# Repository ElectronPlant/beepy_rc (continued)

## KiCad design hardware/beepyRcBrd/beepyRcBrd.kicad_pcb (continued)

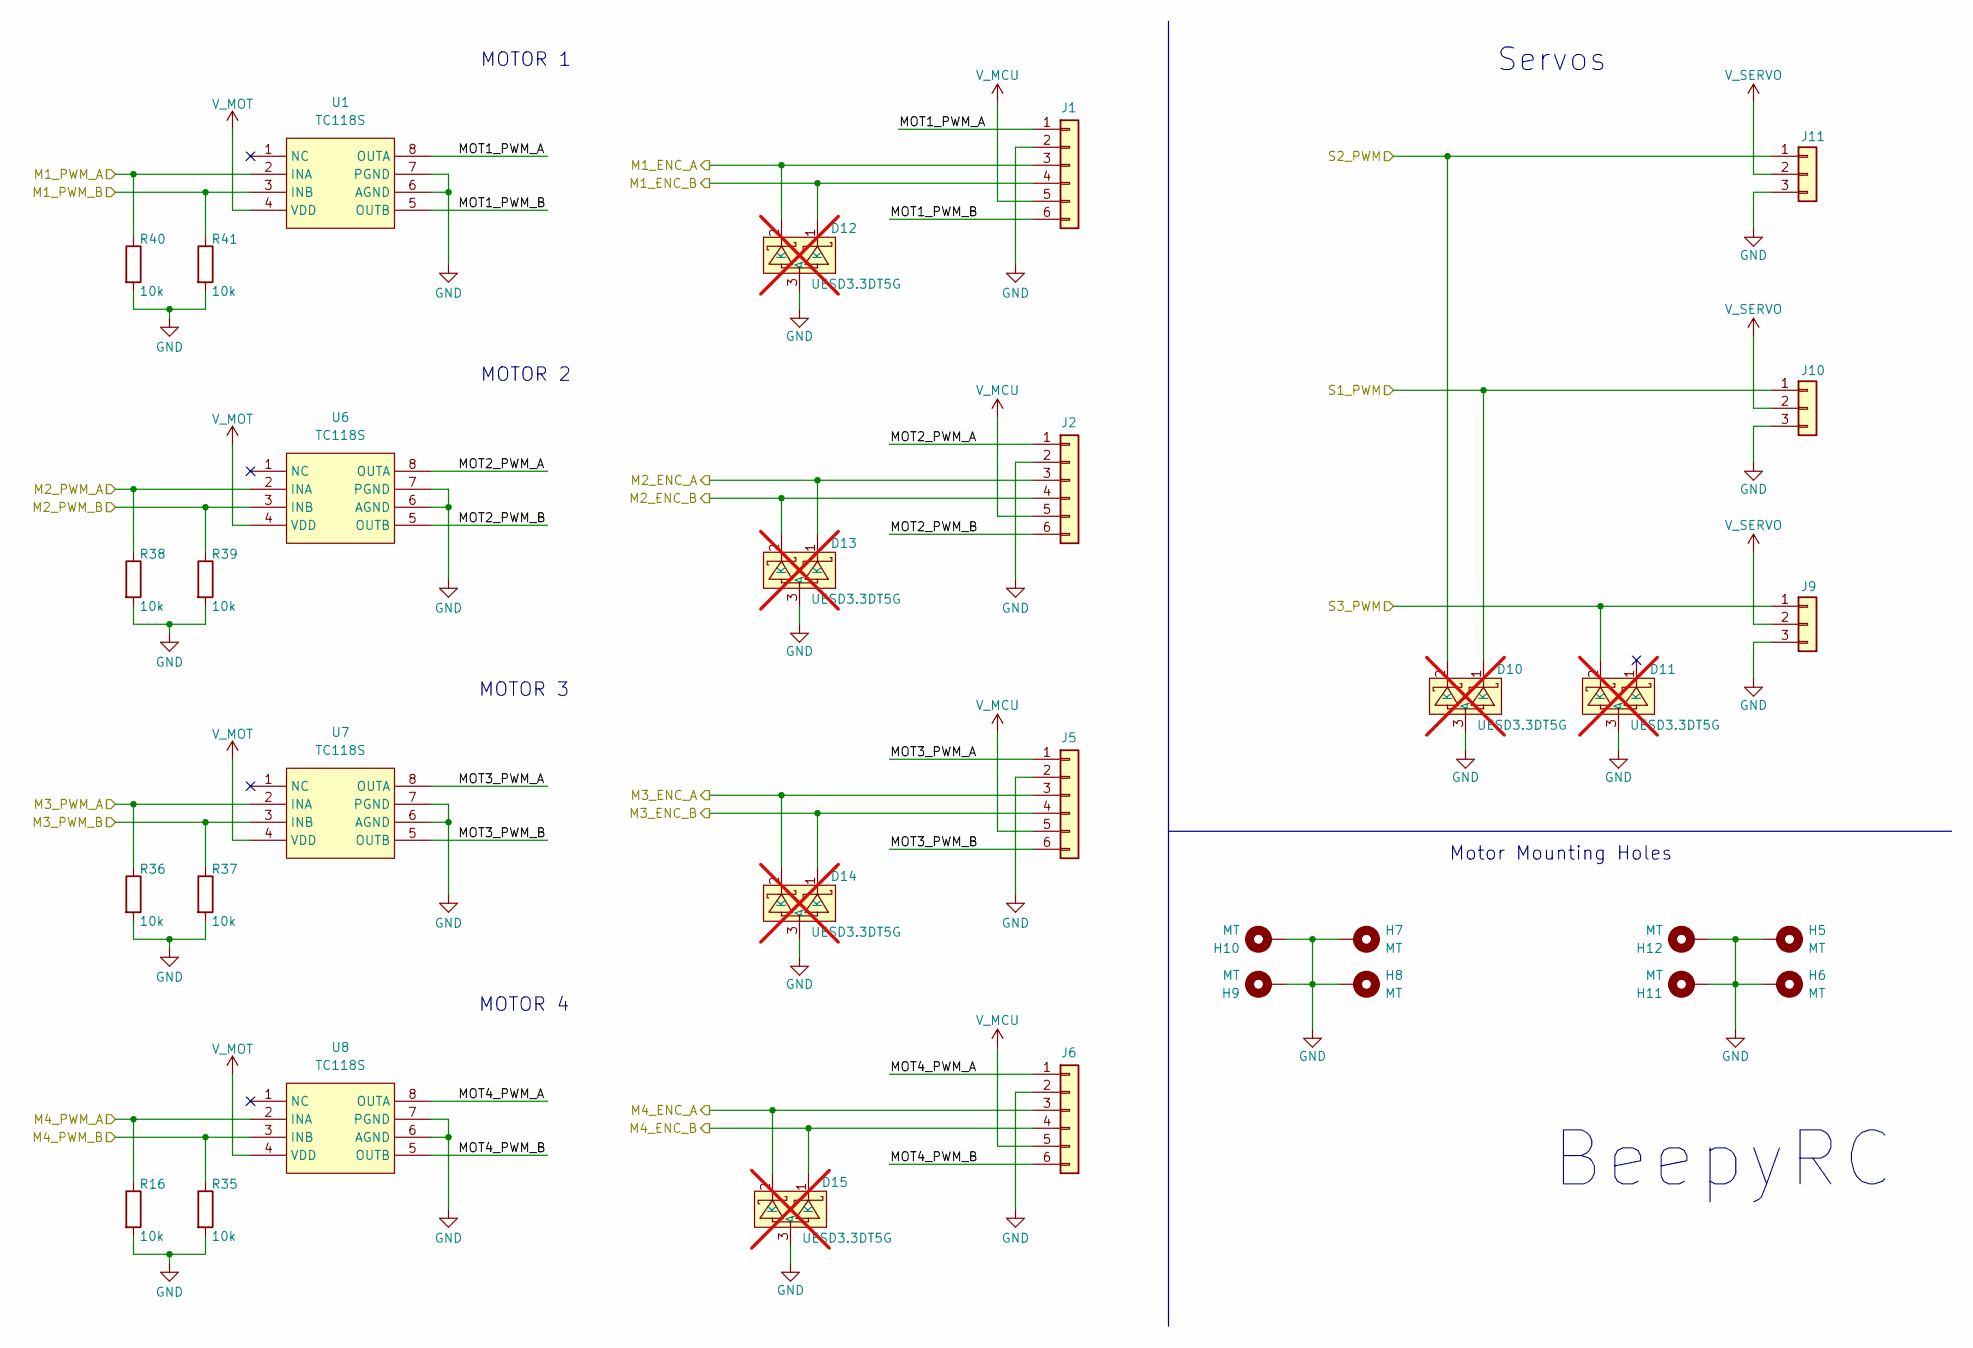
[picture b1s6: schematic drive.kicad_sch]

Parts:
D10, D11, D12, D13, D14, D15: UESD3.3DT5G; SOT-723_L1.2-W0.8-P0.40-LS1.2-BR; LCSC Part C233435; not fitted
H5, H6, H7, H8, H9, H10, H11, H12: MT; MountingHole_2.2mm_M2_DIN965_Pad_TopBottom
J1, J2, J5, J6: Conn_01x06; PinHeader_1x06_P2.54mm_Vertical
J9, J10, J11: Conn_01x03; PinHeader_1x03_P2.54mm_Vertical
R16, R35, R36, R37, R38, R39, R40, R41: 10k; R_0603_1608Metric_Pad0.98x0.95mm_HandSolder
U1, U6, U7, U8: TC118S; SOP-8_L4.9-W3.9-P1.27-LS6.0-BL; LCSC Part C88308

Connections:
/Drive/MOT1_PWM_A: J1.1, U1.8 (OUTA)
/Drive/MOT1_PWM_B: J1.6, U1.5 (OUTB)
/Drive/MOT2_PWM_A: J2.1, U6.8 (OUTA)
/Drive/MOT2_PWM_B: J2.6, U6.5 (OUTB)
/Drive/MOT3_PWM_A: J5.1, U7.8 (OUTA)
/Drive/MOT3_PWM_B: J5.6, U7.5 (OUTB)
/Drive/MOT4_PWM_A: J6.1, U8.8 (OUTA)
/Drive/MOT4_PWM_B: J6.6, U8.5 (OUTB)
/M1_ENC_A: D12.2 (K), J1.3; also elsewhere on the board
/M1_ENC_B: D12.1 (K), J1.4; also elsewhere on the board
/M1_PWM_A: R40.1, U1.2 (INA); also elsewhere on the board
/M1_PWM_B: R41.1, U1.3 (INB); also elsewhere on the board
/M2_ENC_A: D13.1 (K), J2.3; also elsewhere on the board
/M2_ENC_B: D13.2 (K), J2.4; also elsewhere on the board
/M2_PWM_A: R38.1, U6.2 (INA); also elsewhere on the board
/M2_PWM_B: R39.1, U6.3 (INB); also elsewhere on the board
/M3_ENC_A: D14.2 (K), J5.3; also elsewhere on the board
/M3_ENC_B: D14.1 (K), J5.4; also elsewhere on the board
/M3_PWM_A: R36.1, U7.2 (INA); also elsewhere on the board
/M3_PWM_B: R37.1, U7.3 (INB); also elsewhere on the board
/M4_ENC_A: D15.2 (K), J6.3; also elsewhere on the board
/M4_ENC_B: D15.1 (K), J6.4; also elsewhere on the board
/M4_PWM_A: R16.1, U8.2 (INA); also elsewhere on the board
/M4_PWM_B: R35.1, U8.3 (INB); also elsewhere on the board
/SERVO1_PWM: D10.1 (K), J10.1; also elsewhere on the board
/SERVO2_PWM: D10.2 (K), J11.1; also elsewhere on the board
/SERVO3_PWM: D11.2 (K), J9.1; also elsewhere on the board
GND: D10.3 (A), D11.3 (A), D12.3 (A), D13.3 (A), D14.3 (A), D15.3 (A), H5.1, H6.1, H7.1, H8.1, H9.1, H10.1, H11.1, H12.1, J1.2, J2.2, J5.2, J6.2, J9.3, J10.3, J11.3, R16.2, R35.2, R36.2, R37.2, R38.2, R39.2, R40.2, R41.2, U1.6 (AGND), U1.7 (PGND), U6.6 (AGND), U6.7 (PGND), U7.6 (AGND), U7.7 (PGND), U8.6 (AGND), U8.7 (PGND); also elsewhere on the board
V_MCU: J1.5, J2.5, J5.5, J6.5; also elsewhere on the board
V_MOT: U1.4 (VDD), U6.4 (VDD), U7.4 (VDD), U8.4 (VDD); also elsewhere on the board
V_SERVO: J9.2, J10.2, J11.2; also elsewhere on the board

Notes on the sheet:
MOTOR 3
Motor Mounting Holes
MOTOR 4
MOTOR 2
BeepyRC
Servos
MOTOR 1

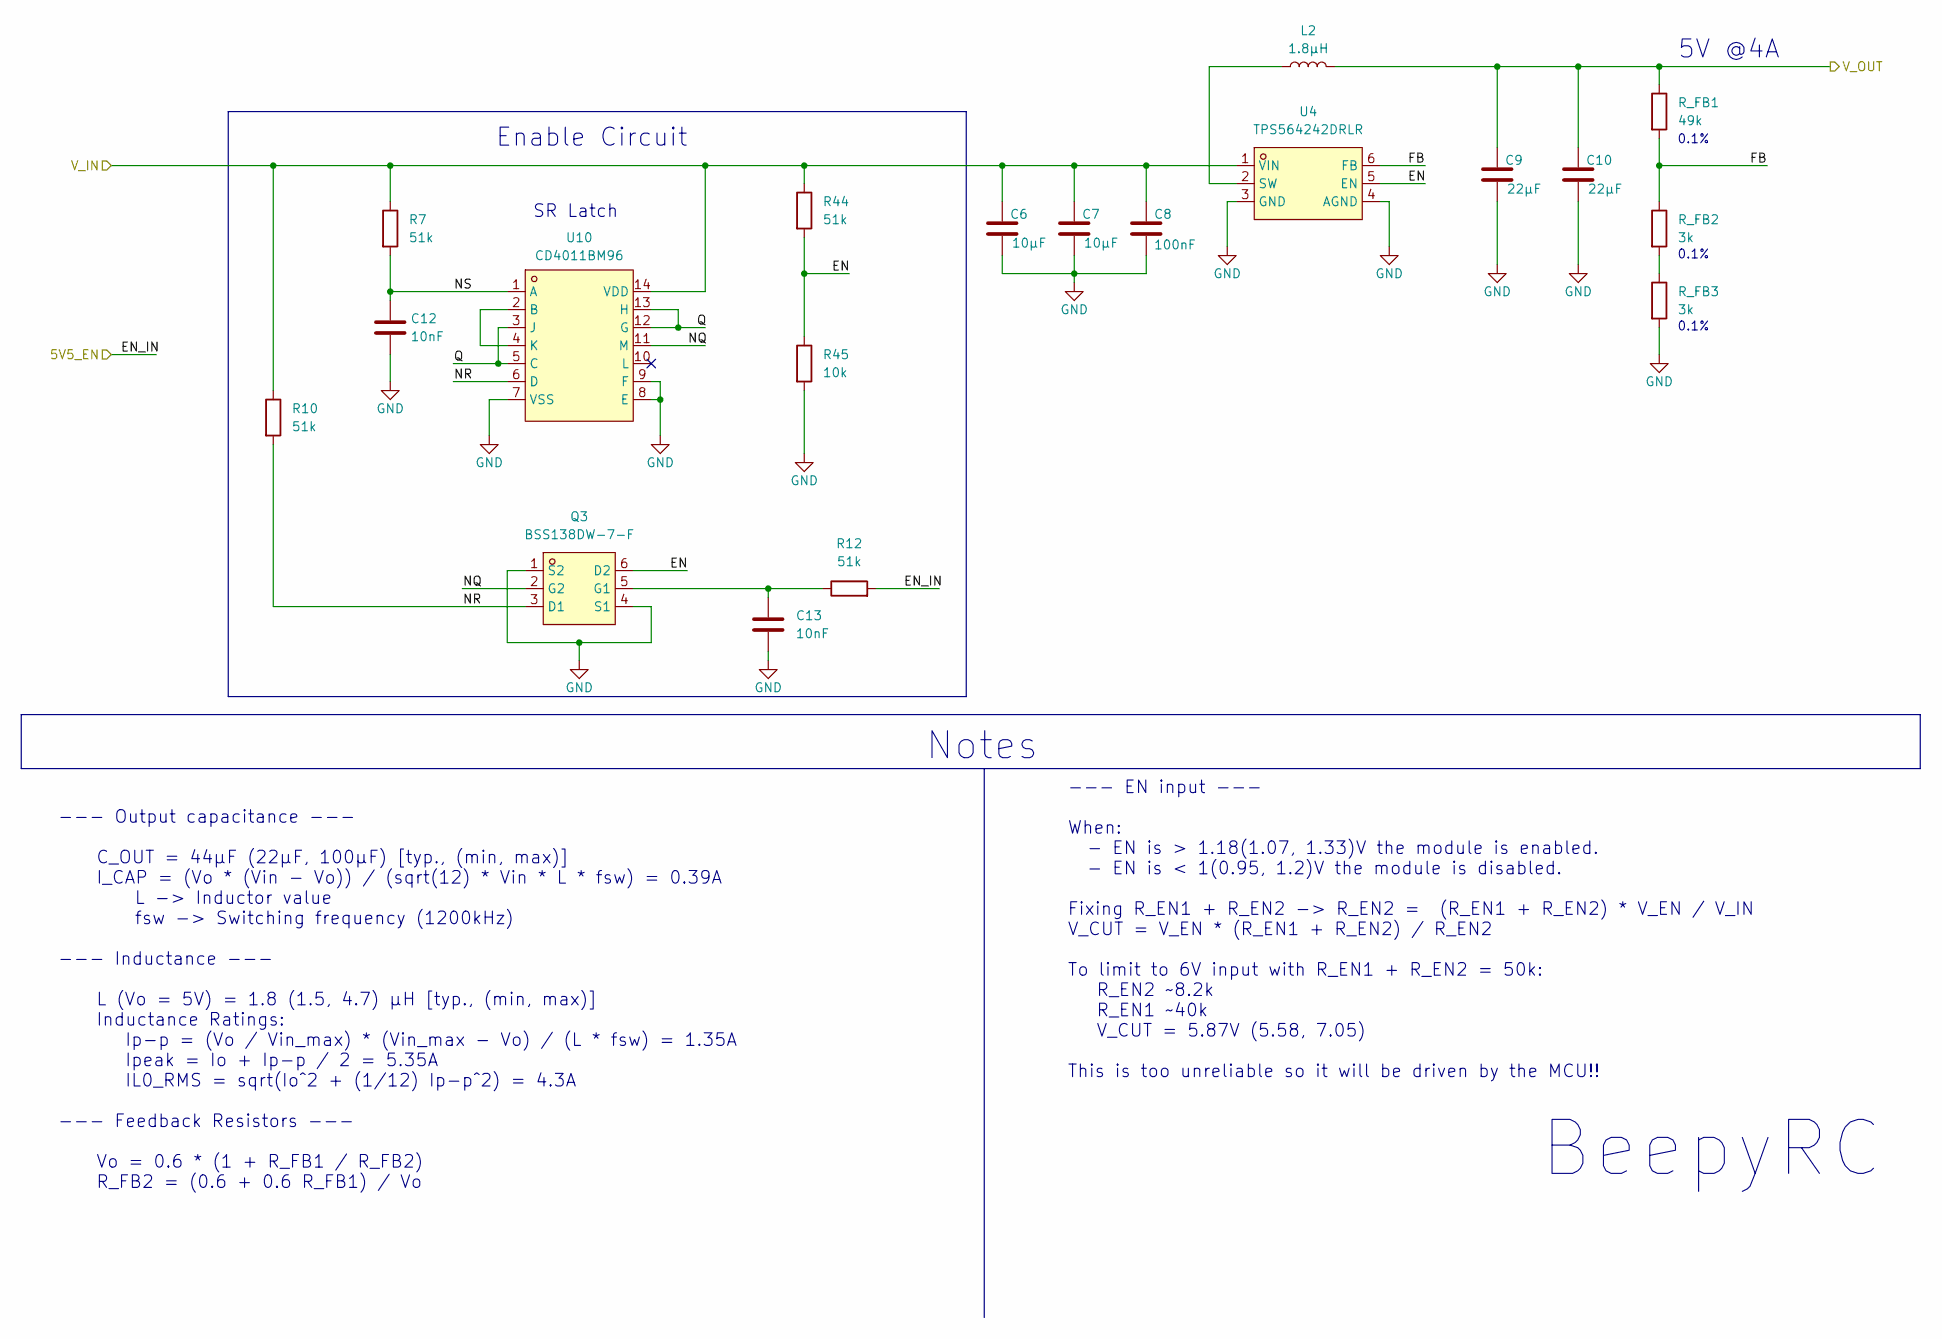
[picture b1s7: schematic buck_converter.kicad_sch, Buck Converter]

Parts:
C6, C7: 10μF; C_0603_1608Metric_Pad1.08x0.95mm_HandSolder
C8: 100nF; C_0603_1608Metric_Pad1.08x0.95mm_HandSolder
C9, C10: 22μF; C_0603_1608Metric_Pad1.08x0.95mm_HandSolder
C12, C13: 10nF; C_0603_1608Metric_Pad1.08x0.95mm_HandSolder
L2: 1.8μH; IND-SMD_L7.0-W6.6_MCW-0650-220
Q3: BSS138DW-7-F; SC-70-6_L2.2-W1.3-P0.65-LS2.1-TL; LCSC Part C154900
R7, R10, R12, R44: 51k; R_0603_1608Metric_Pad0.98x0.95mm_HandSolder
R45: 10k; R_0603_1608Metric_Pad0.98x0.95mm_HandSolder
R_FB1: 49k; R_0603_1608Metric_Pad0.98x0.95mm_HandSolder
R_FB2, R_FB3: 3k; R_0603_1608Metric_Pad0.98x0.95mm_HandSolder
U4: TPS564242DRLR; SOT-5X3-6_W1.6-L1.2-P0.50-LS1.6-BL; LCSC Part C5219267
U10: CD4011BM96; SOIC-14_L8.7-W3.9-P1.27-LS6.0-BL; LCSC Part C48466

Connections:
/EN_BAT: R12.2; also elsewhere on the board
/Power/5VBuck/EN: Q3.6 (D2), R44.2, R45.1, U4.5 (EN)
/Power/5VBuck/FB: R_FB1.2, R_FB2.1, U4.6 (FB)
/Power/5VBuck/NQ: Q3.2 (G2), U10.11 (M)
/Power/5VBuck/NR: Q3.3 (D1), R10.2, U10.6 (D)
/Power/5VBuck/NS: C12.1, R7.2, U10.1 (A)
/Power/5VBuck/Q: U10.3 (J), U10.5 (C), U10.12 (G), U10.13 (H)
GND: C6.2, C7.2, C8.2, C9.2, C10.2, C12.2, C13.2, Q3.1 (S2), Q3.4 (S1), R45.2, R_FB3.2, U4.3 (GND), U4.4 (AGND), U10.7 (VSS), U10.8 (E), U10.9 (F); also elsewhere on the board
unnamed: C13.1, Q3.5 (G1), R12.1
unnamed: R_FB2.2, R_FB3.1
unnamed: L2.1, U4.2 (SW)
unnamed: U10.2 (B), U10.4 (K)
V_MOT: C6.1, C7.1, C8.1, R7.1, R10.1, R44.1, U4.1 (VIN), U10.14 (VDD); also elsewhere on the board
V_SERVO: C9.1, C10.1, L2.2, R_FB1.1; also elsewhere on the board

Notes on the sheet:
0.1%
5V @4A
SR Latch
Enable Circuit
--- Output capacitance --- C_OUT = 44μF (22μF, 100μF) [typ., (min, max)] I_CAP = (Vo * (Vin - Vo)) / (sqrt(12) * Vin * L * fsw) = 0.39A L -> Inductor value fsw -> Switching frequency (1200kHz) --- Inductance --- L (Vo = 5V) = 1.8 (1.5, 4.7) μH [typ., (min, max)] Inductance Ratings: Ip-p = (Vo / Vin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
BeepyRC
--- EN input --- When: - EN is > 1.18(1.07, 1.33)V the module is enabled. - EN is < 1(0.95, 1.2)V the module is disabled. Fixing R_EN1 + R_EN2 -> R_EN2 = (R_EN1 + R_EN2) * V_EN / V_IN V_CUT = V_EN * (R_EN1 + R_EN2) / R_EN2 To limit to 6V input with R_EN1 + R_EN2 = 50k: R_EN2 ~8.2k R_EN1 ~40k V_CUT 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
Notes

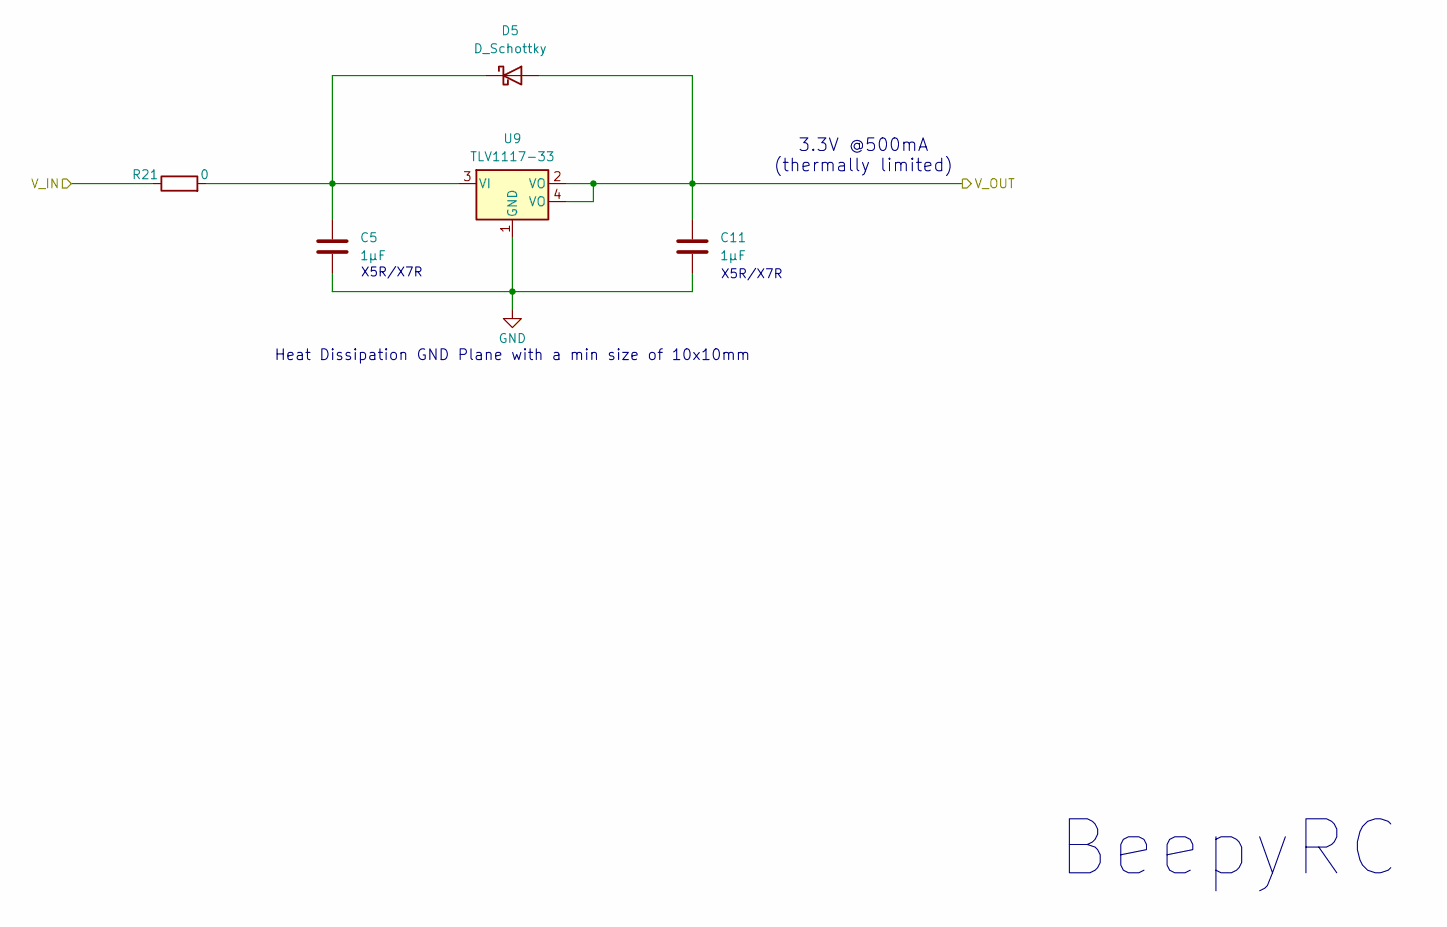
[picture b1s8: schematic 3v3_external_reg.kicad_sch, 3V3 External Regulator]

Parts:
C5, C11: 1μF; C_0603_1608Metric_Pad1.08x0.95mm_HandSolder
D5: D_Schottky; D_SOD-323
R21: 0; R_0603_1608Metric_Pad0.98x0.95mm_HandSolder
U9: TLV1117-33; SOT-223_L6.5-W3.5-P2.30-LS7.0-BR

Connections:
GND: C5.2, C11.2, U9.1 (GND); also elsewhere on the board
unnamed: C5.1, D5.1 (K), R21.2, U9.3 (VI)
V_3V3_EXT: C11.1, D5.2 (A), U9.2 (VO), U9.4 (VO); also elsewhere on the board
V_VTX: R21.1; also elsewhere on the board

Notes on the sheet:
3.3V @500mA (thermally limited)
X5R/X7R
BeepyRC
Heat Dissipation GND Plane with a min size of 10x10mm

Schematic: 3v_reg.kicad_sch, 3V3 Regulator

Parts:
C3, C4: 1μF; C_0603_1608Metric_Pad1.08x0.95mm_HandSolder
U5: MC33275ST-3.3T3G; SOT-223_L6.5-W3.5-P2.30-LS7.0-BR; LCSC Part C153747

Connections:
+5V: C3.1, U5.1 (VIN); also elsewhere on the board
GND: C3.2, C4.2, U5.2 (GND), U5.4 (TAB); also elsewhere on the board
V_MCU: C4.1, U5.3 (VOUT); also elsewhere on the board

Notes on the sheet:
BeepyRC
Heat Dissipation GND Plane with a min size of 10x10mm
3.3V @300mA
X5R/X7R

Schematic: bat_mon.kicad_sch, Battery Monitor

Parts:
C1: 5.1nF; C_0603_1608Metric_Pad1.08x0.95mm_HandSolder
C2: 18nF; C_0603_1608Metric_Pad1.08x0.95mm_HandSolder
R11: 30k; R_0603_1608Metric_Pad0.98x0.95mm_HandSolder
R42: 40k; R_0603_1608Metric_Pad0.98x0.95mm_HandSolder
R43: 10k; R_0603_1608Metric_Pad0.98x0.95mm_HandSolder
Rs1: 17m; R_1206_3216Metric_Pad1.30x1.75mm_HandSolder
U3: INA139; SOT-23-5

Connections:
/Power/BatteryMonitor/V_BAT: R42.1, Rs1.1, U3.3 (+), U3.5 (V+); also elsewhere on the board
/V_BAT_MEAS: C2.1, R42.2, R43.1; also elsewhere on the board
/V_I_SENSE: C1.1, R11.1, U3.1; also elsewhere on the board
GND: C1.2, C2.2, R11.2, R43.2, U3.2 (GND); also elsewhere on the board
V_MOT: Rs1.2, U3.4 (-); also elsewhere on the board

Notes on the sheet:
V_BAT_MEAS = 0.24 * V_BAT
--- INA139 --- Output Voltage: Vo = Is * 1mA/V * R_L Vs full scale = 100mV (could also be 50mV to 500mV) R_L -> Set to generate ~3V at 6A (<50kOhm, ADC external resistance limit) C_L -> Low pass filter with a cut-off frequency at ~1kHz
--- Battery Voltage --- 2S battery range 6 - 8.4V, with 7.4 nominal Maximum ranges 6 - 12V --> Limited by the N20 motors R_SENSE is set to: 1. Be <50kOhm (ADC external resistance limit), 2. V_BAT_MEAS is ~3V @ 12V 3. Low-pass filter with Fc ~1kHz
Is = 0.51A/V * V_I_SENSE (fc = 1.04kHz)
--- Shunt Resistor --- Vs = 100mV with max current max(Is) = 6A > (4 * 0.35A for the motors + 4A for the 5.5V rail) Rs = Vs / max(Is) = ~17mOhm Power Rating: 0.6W
0.1%
BeepyRC

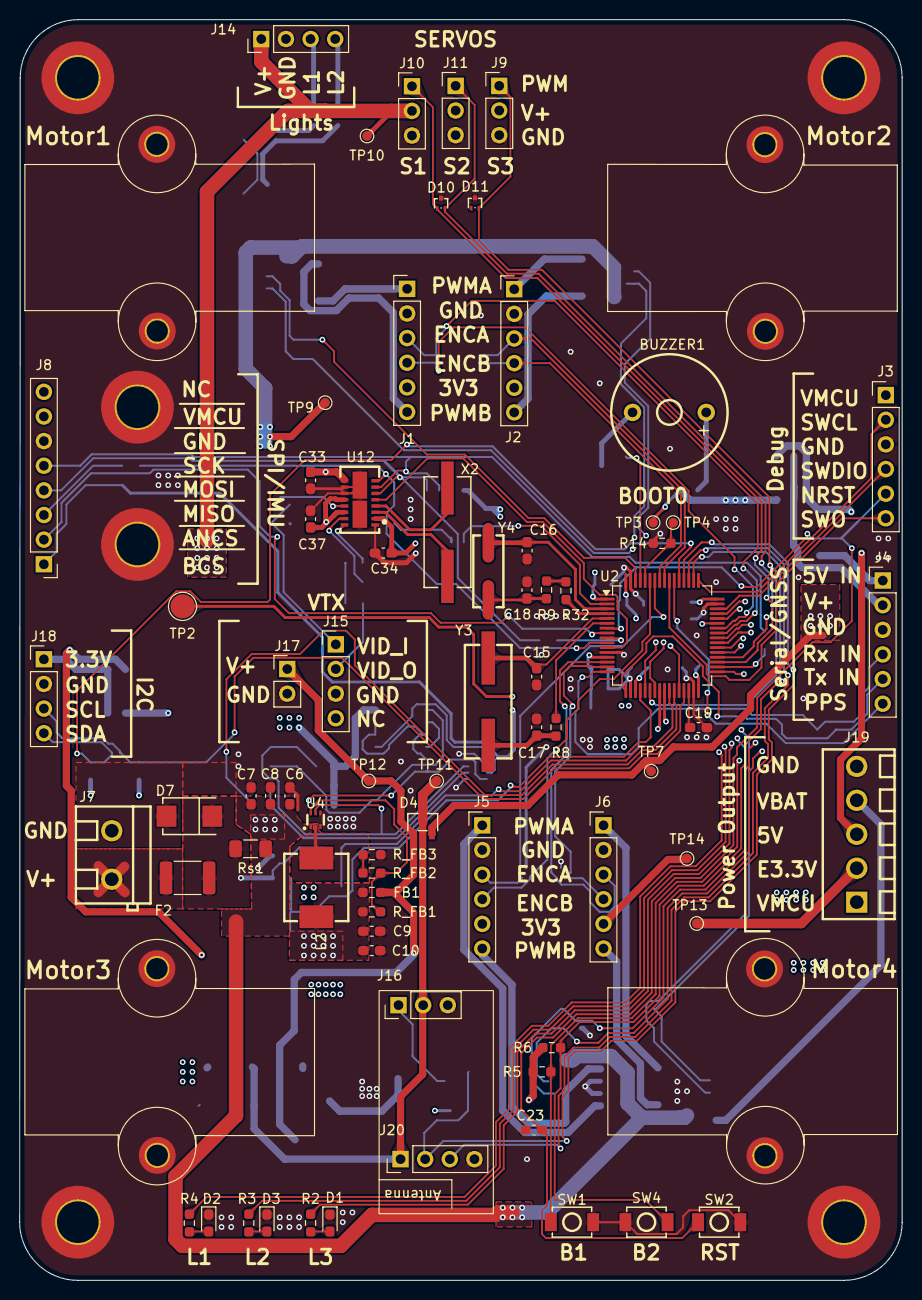
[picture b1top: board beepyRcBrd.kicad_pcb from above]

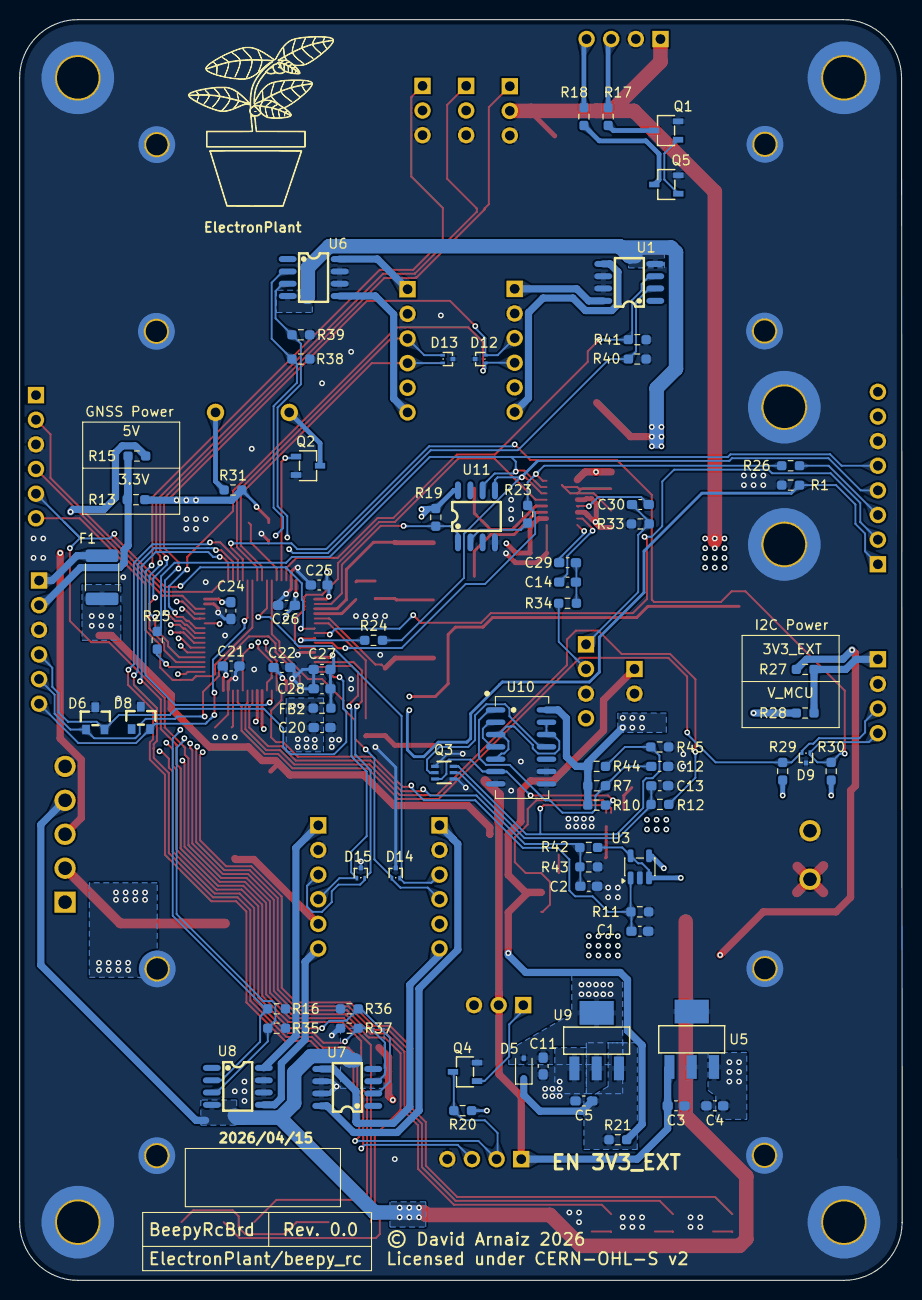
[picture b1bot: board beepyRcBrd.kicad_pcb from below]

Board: 4 copper layers, 91.0 x 130.0 mm, 171 parts (78 on the bottom side), 112 nets.

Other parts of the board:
Motor1, Motor2, Motor3, Motor4: Motor

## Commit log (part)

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2025-07-01 feat: fist commit
    first commit includes:
    - Documentaion setup.
    - STM32 drivers.
    - Basic Makefile.
    - Minimal app with basic SBUS support.
    - Licensing information.
2025-07-05 feat: adding support for FreeRTOS
2025-07-05 docs: adding more temporal information in the SBUS documentation
2025-07-06 docs: adding intellisense documentation
2025-07-09 chore: reordered files
2025-07-16 feat: removing hall dependencies for systick
2025-08-06 chore: porting from windows to ubuntu
2025-08-07 feat: adding new platform utils
2025-08-07 feat: preliminary motion support
2025-08-10 chore: update clang-format
2025-08-21 chore: clang-format alignment fix - aligning declarations and comments
2025-09-11 feat: adding circullar allocator lib
2025-11-27 feat: improving platform
2025-11-27 feat: preliminary rc support
2025-11-27 refactor: clean common RX interface
2025-11-27 chore: updated function docstrings
2025-11-30 feat: RC module tested
2025-11-30 refactor: removed legacy TODOs
2025-12-07 feat: Preliminary support for encoders
2025-12-08 feat: completed support for multiple encoders
2025-12-10 test: testing PWM + encoders
2025-12-17 refactor: generalize the PWM timer implementation
2025-12-17 platform: added max, min and saturate utils
2025-12-17 chore: adding missing asserts on the encoder module
2025-12-25 refactor: clean up pwm timer and encoder dirvers
2025-12-25 feat: motor driver
2025-12-25 feat: add the RC module back
2025-12-25 chore: ignoring hardware for now
2025-12-26 refactor: set ports to their own place
2025-12-31 refactor: generalize Rx bus handling
2025-12-31 typo: fix abstraction to abstraction layer
2025-12-31 format: add formatting
2025-12-31 feat: adding support for multiple motors
2026-02-28 feat: brd schematics v0.0
2026-03-01 fix: motor PWM pulled down
2026-03-01 temp: adding queue to motion task
2026-03-01 feat: adding servo motor support
2026-03-01 fix: net names
2026-03-01 chore: updating HW documentation
2026-03-01 fix: passing schematics ERC rules
2026-04-18 chore: update LICENSES
2026-04-18 feat: completed beepyRcBrd_rev_0_0.pdf
2026-04-19 chore: unify licensing information
2026-04-26 refactor: move board specific defines to the target file
2026-05-10 feat: adding ABS for the utils
2026-05-10 feat: RC improve error handling and added RC inputs
2026-05-10 fix: remove compilation warning on print
2026-05-10 feat: adding travel based control for servos
2026-05-10 feat: adding basic implementaion for controller
2026-05-10 feat: RC input to PWM output
2026-05-31 feat: Controller + UI
2026-05-31 chore: improving gitignore
2026-05-31 feat: add support for beepyRcBrd
